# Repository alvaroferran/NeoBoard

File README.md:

# NeoBoard

<br>

NeoBoard is a robotics controller shield for the [NanoPi Neo Air](http://nanopi.io/nanopi-neo-air.html) SBC. It can drive two DC motors, has four extra 5V GPIOs and an ADC to read the battery level from the Linux board. It also includes a 1S LiPo battery charger, a 3.5A boost circuit to ramp the voltage up to 5V for the motors and a hardware-based motor disconnect in case of low battery.

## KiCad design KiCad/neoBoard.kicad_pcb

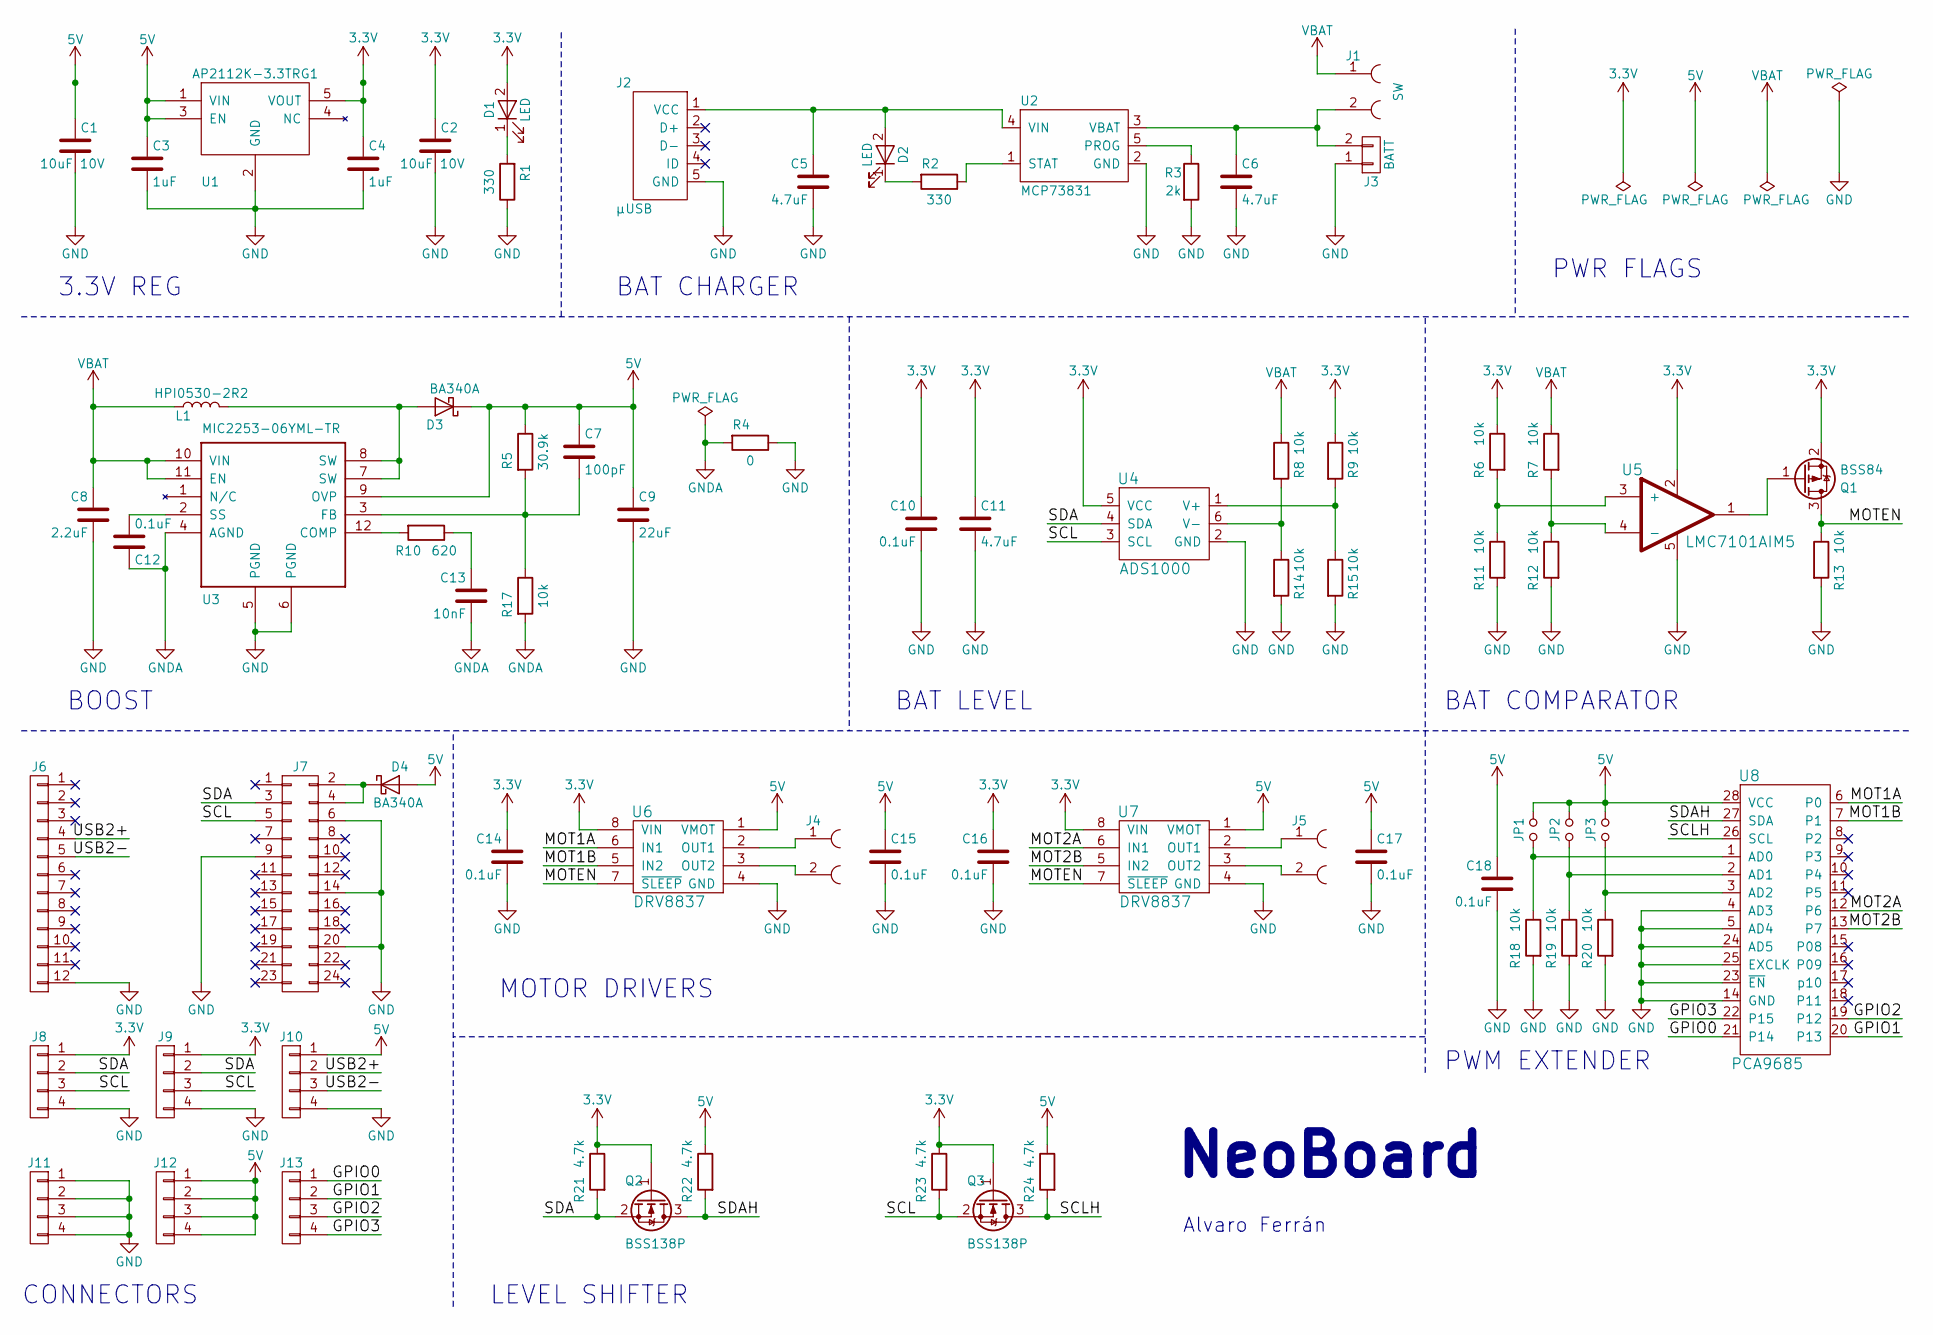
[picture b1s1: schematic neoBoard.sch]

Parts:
C1, C2: 10uF 10V; C_0603
C3, C4: 1uF; C_0603
C5, C6, C11: 4.7uF; C_0402
C7: 100pF; C_0603
C8: 2.2uF; C_0603
C9: 22uF; C_0805
C10, C14, C15, C16, C17, C18: 0.1uF; C_0402
C12: 0.1uF; C_0603
C13: 10nF; C_0603
D1, D2: LED; LED_0603
D3, D4: BA340A; D_SMA
J1: SW; TerminalBlock_Pheonix_MPT-2.54mm_2pol
J2: μUSB; USB_Micro-B
J3: BATT; Pin_Header_Angled_1x02_Pitch2.54mm
J4, J5: TerminalBlock_Pheonix_MPT-2.54mm_2pol
J6: CONN_01X12_Straight; Pin_Header_Straight_1x12_Pitch2.54mm
J7: CONN_02X12_Straight; Pin_Header_Straight_2x12_Pitch2.54mm
J8, J9, J10, J11, J12, J13: CONN_01X04_Straight; Pin_Header_Straight_1x04_Pitch2.54mm
JP1, JP2, JP3: Jumper_NO; GS2
L1: HPI0530-2R2
Q1: BSS84; SOT-23
Q2, Q3: BSS138P; SOT-23
R1, R2: 330; R_0402
R3: 2k; R_0402
R4: 0; R_0603
R5: 30.9k; R_0603
R6, R7, R8, R9, R11, R12, R13, R14, R15, R18, R19, R20: 10k; R_0402
R10: 620; R_0603
R17: 10k; R_0603
R21, R22, R23, R24: 4.7k; R_0402
U1: AP2112K-3.3TRG1; SOT-23-5
U2: MCP73831; SOT-23-5
U3: MIC2253-06YML-TR
U4: ADS1000; SOT-23-6
U5: LMC7101AIM5; SOT-23-5
U6, U7: DRV8837; WSON-8
U8: PCA9685; TSSOP-28

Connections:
3.3V: C2.1, C4.1, C10.1, C11.1, C14.1, C16.1, D1.2 (A), J8.1, J9.1, Q1.2 (S), Q2.1 (G), Q3.1 (G), R6.1, R9.1, R21.1, R23.1, U1.5 (VOUT), U4.5 (VCC), U5.2, U6.8 (VIN), U7.8 (VIN)
5V: C1.1, C3.1, C7.1, C9.1, C15.1, C17.1, C18.1, D3.1 (K), D4.2 (A), J10.1, J12.1, J12.2, J12.3, J12.4, JP1.2, JP2.2, JP3.2, R5.1, R22.1, R24.1, U1.1 (VIN), U1.3 (EN), U3.9 (OVP), U6.1 (VMOT), U7.1 (VMOT), U8.28 (VCC)
/GPIO0: J13.1, U8.21 (P14)
/GPIO1: J13.2, U8.20 (P13)
/GPIO2: J13.3, U8.19 (P12)
/GPIO3: J13.4, U8.22 (P15)
/MOT1A: U6.6 (IN1), U8.6 (P0)
/MOT1B: U6.5 (IN2), U8.7 (P1)
/MOT2A: U7.6 (IN1), U8.12 (P6)
/MOT2B: U7.5 (IN2), U8.13 (P7)
/MOTEN: Q1.3 (D), R13.1, U6.7 (~SLEEP), U7.7 (~SLEEP)
/SCL: J7.5, J8.3, J9.3, Q3.2 (S), R23.2, U4.3 (SCL)
/SCLH: Q3.3 (D), R24.2, U8.26 (SCL)
/SDA: J7.3, J8.2, J9.2, Q2.2 (S), R21.2, U4.4 (SDA)
/SDAH: Q2.3 (D), R22.2, U8.27 (SDA)
/USB2+: J6.4, J10.2
/USB2-: J6.5, J10.3
GND: C1.2, C2.2, C3.2, C4.2, C5.2, C6.2, C8.2, C9.2, C10.2, C11.2, C14.2, C15.2, C16.2, C17.2, C18.2, J2.5 (GND), J3.1, J6.12, J7.6, J7.9, J7.14, J7.20, J8.4, J9.4, J10.4, J11.1, J11.2, J11.3, J11.4, R1.1, R3.2, R4.1, R11.2, R12.2, R13.2, R14.2, R15.2, R18.2, R19.2, R20.2, U1.2 (GND), U2.2 (GND), U3.5 (PGND), U3.6 (PGND), U4.2 (GND), U5.5, U6.4 (GND), U7.4 (GND), U8.4 (AD3), U8.5 (AD4), U8.14 (GND), U8.23 (~EN), U8.24 (AD5), U8.25 (EXCLK)
GNDA: C12.1, C13.2, R4.2, R17.2, U3.4 (AGND)
unnamed: C5.1, D2.2 (A), J2.1 (VCC), U2.4 (VIN)
unnamed: C6.1, J1.2, J3.2, U2.3 (VBAT)
unnamed: C7.2, R5.2, R17.1, U3.3 (FB)
unnamed: C12.2, U3.2 (SS)
unnamed: C13.1, R10.1
unnamed: D1.1 (K), R1.2
unnamed: D2.1 (K), R2.2
unnamed: D3.2 (A), L1.2, U3.7 (SW), U3.8 (SW)
unnamed: D4.1 (K), J7.2, J7.4
unnamed: J4.1, U6.2 (OUT1)
unnamed: J4.2, U6.3 (OUT2)
unnamed: J5.1, U7.2 (OUT1)
unnamed: J5.2, U7.3 (OUT2)
unnamed: JP1.1, R18.1, U8.1 (AD0)
unnamed: JP2.1, R19.1, U8.2 (AD1)
unnamed: JP3.1, R20.1, U8.3 (AD2)
unnamed: Q1.1 (G), U5.1
unnamed: R2.1, U2.1 (STAT)
unnamed: R3.1, U2.5 (PROG)
unnamed: R10.2, U3.12 (COMP)
unnamed: R6.2, R11.1, U5.3 (+)
unnamed: R7.2, R12.1, U5.4 (-)
unnamed: R8.2, R14.1, U4.6 (V-)
unnamed: R9.2, R15.1, U4.1 (V+)
VBAT: C8.1, J1.1, L1.1, R7.1, R8.1, U3.10 (VIN), U3.11 (EN)

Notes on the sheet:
NeoBoard
Alvaro Ferrán
3.3V REG
BAT CHARGER
BOOST
MOTOR DRIVERS
BAT COMPARATOR
BAT LEVEL
PWM EXTENDER
CONNECTORS
LEVEL SHIFTER
PWR FLAGS

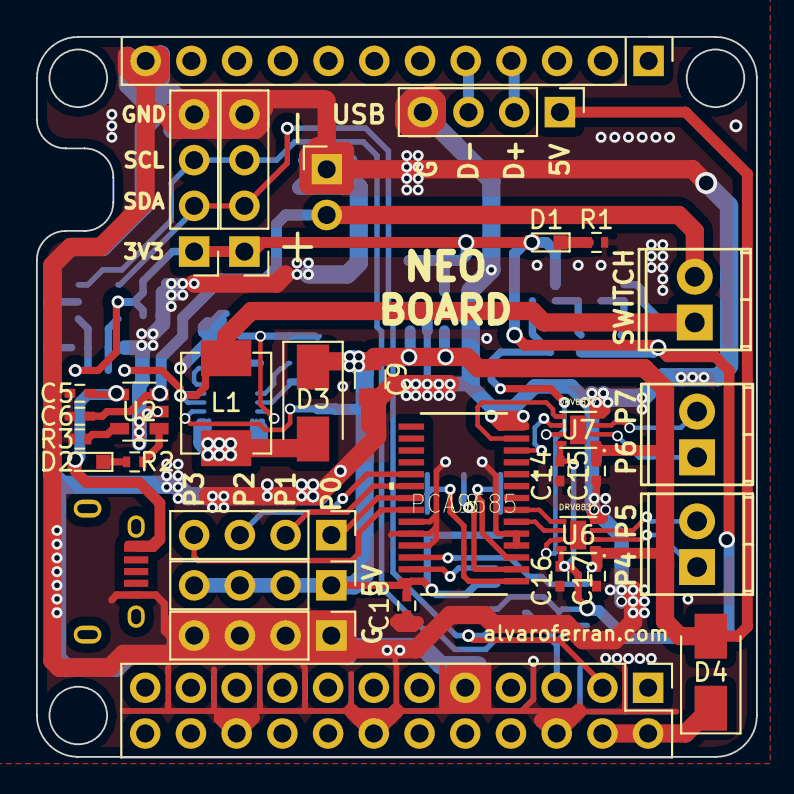
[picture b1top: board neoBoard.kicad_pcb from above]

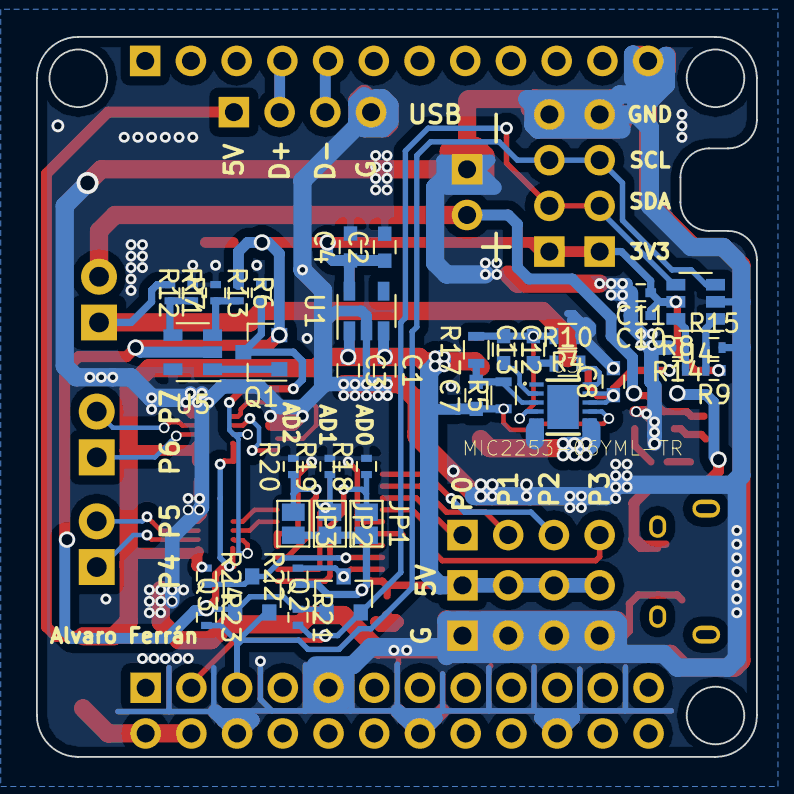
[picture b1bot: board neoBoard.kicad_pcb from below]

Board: 2 copper layers, 40.0 x 40.0 mm, 73 parts (40 on the bottom side), 44 nets.

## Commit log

2017-08-18 Schematic
2017-08-18 Schematic: battery charger
2017-08-22 Schematic: battery inversion protection
2017-08-22 Schematic: motor decoupling caps added
2017-08-23 Schematic: ADC added
2017-08-23 Schematic: PWM added
2017-08-24 Schematic: Connectors added
2017-08-24 Schematic: ERC passed
2017-08-24 Schematic: Packages changed
2017-08-25 Schematic: Packages changed
    Schematic: Packages changed
2017-08-25 Board
2017-08-28 Schematic: Level shifter
2017-08-28 Schematic: Protection diode
2017-08-28 Schematic: Batt inv removed
2017-08-29 Board: components in place
2017-08-31 3D model
2017-09-01 README added
2017-09-05 3D: OBJ added
2017-09-05 3D scale corrected
2017-09-05 3D scale corrected OBJ
2017-09-11 PCB updated
2017-09-22 Improved GND connections
2017-09-22 Change PCA9670 to PCA9685
2017-09-25 Charger track changed from 16mil to 24mil
2017-10-06 Boost circuit re-routed
2017-10-06 Silkscreen fixes
2017-10-16 Silkscreen changes
2017-11-08 Added python classes for PCA9685 and ADS1000 control
2017-11-08 Created Hardware folder
2017-11-09 Example scripts added
2017-11-14 Servo control and frequency selection added
2017-11-14 Servo control example added
2017-11-14 Map function renamed to avoid confusion with native function
2017-11-14 Motor and servo example added
2017-11-28 Differential Drive class added
2017-11-28 Differential Drive example added
